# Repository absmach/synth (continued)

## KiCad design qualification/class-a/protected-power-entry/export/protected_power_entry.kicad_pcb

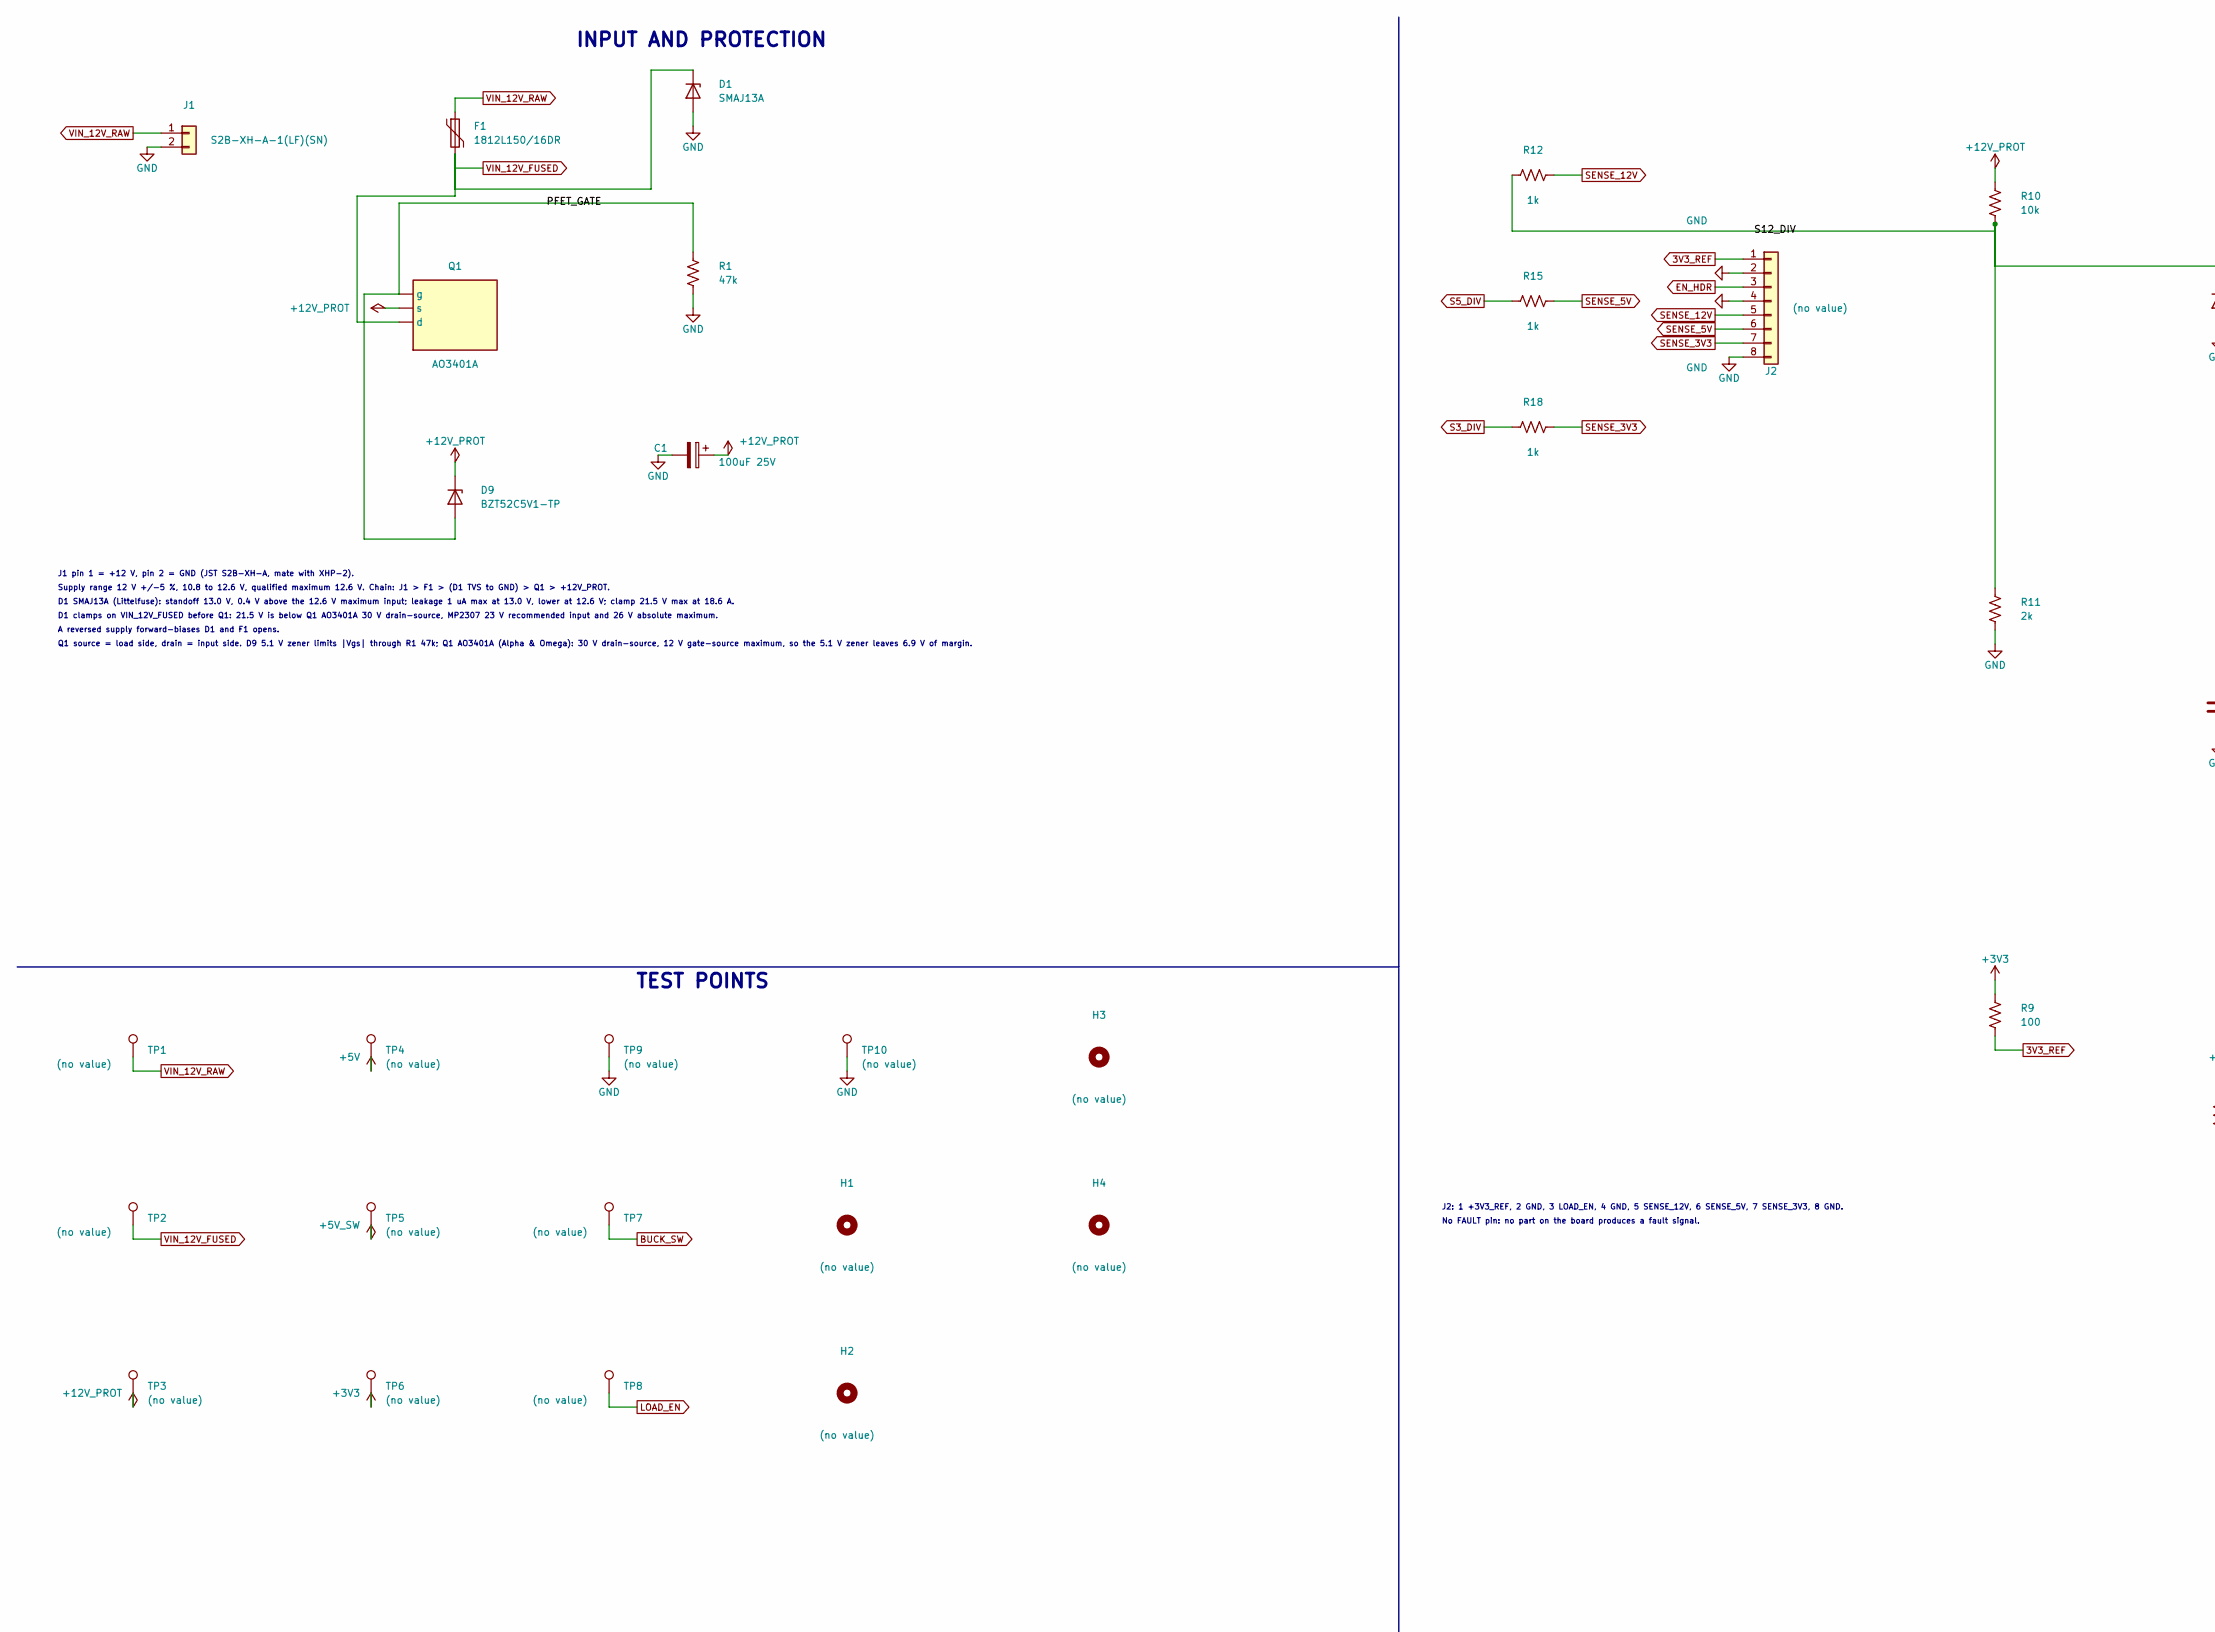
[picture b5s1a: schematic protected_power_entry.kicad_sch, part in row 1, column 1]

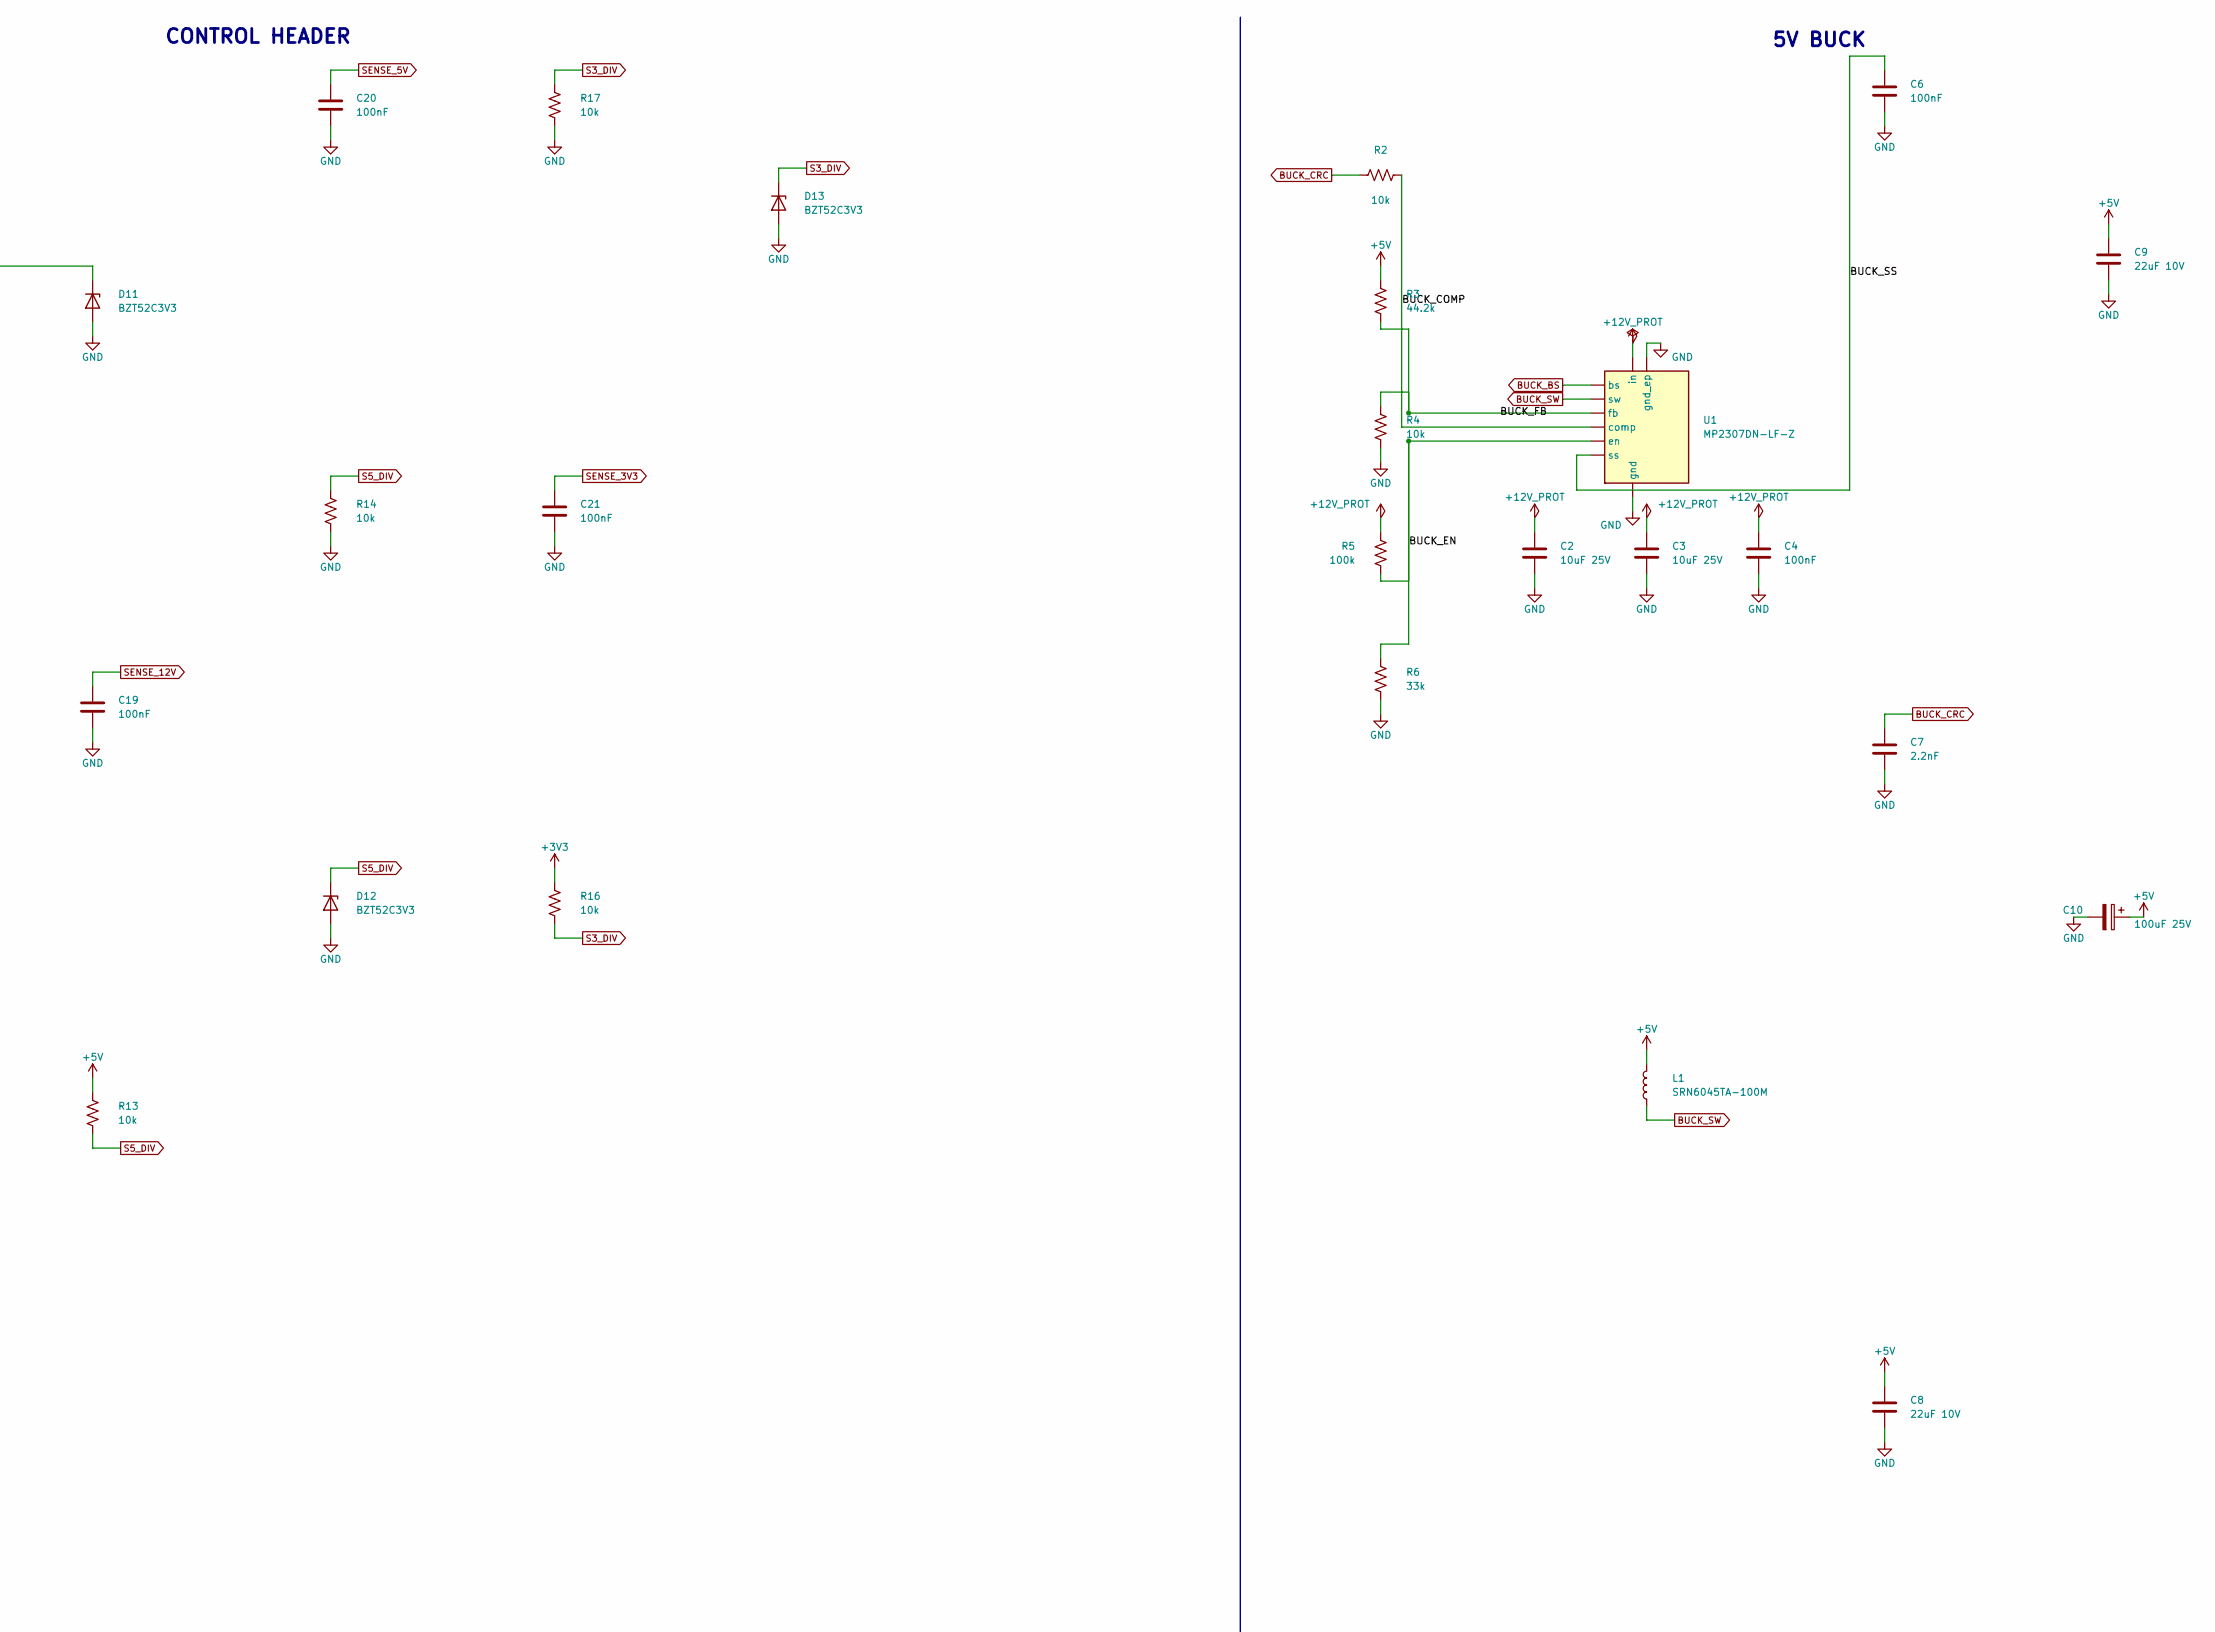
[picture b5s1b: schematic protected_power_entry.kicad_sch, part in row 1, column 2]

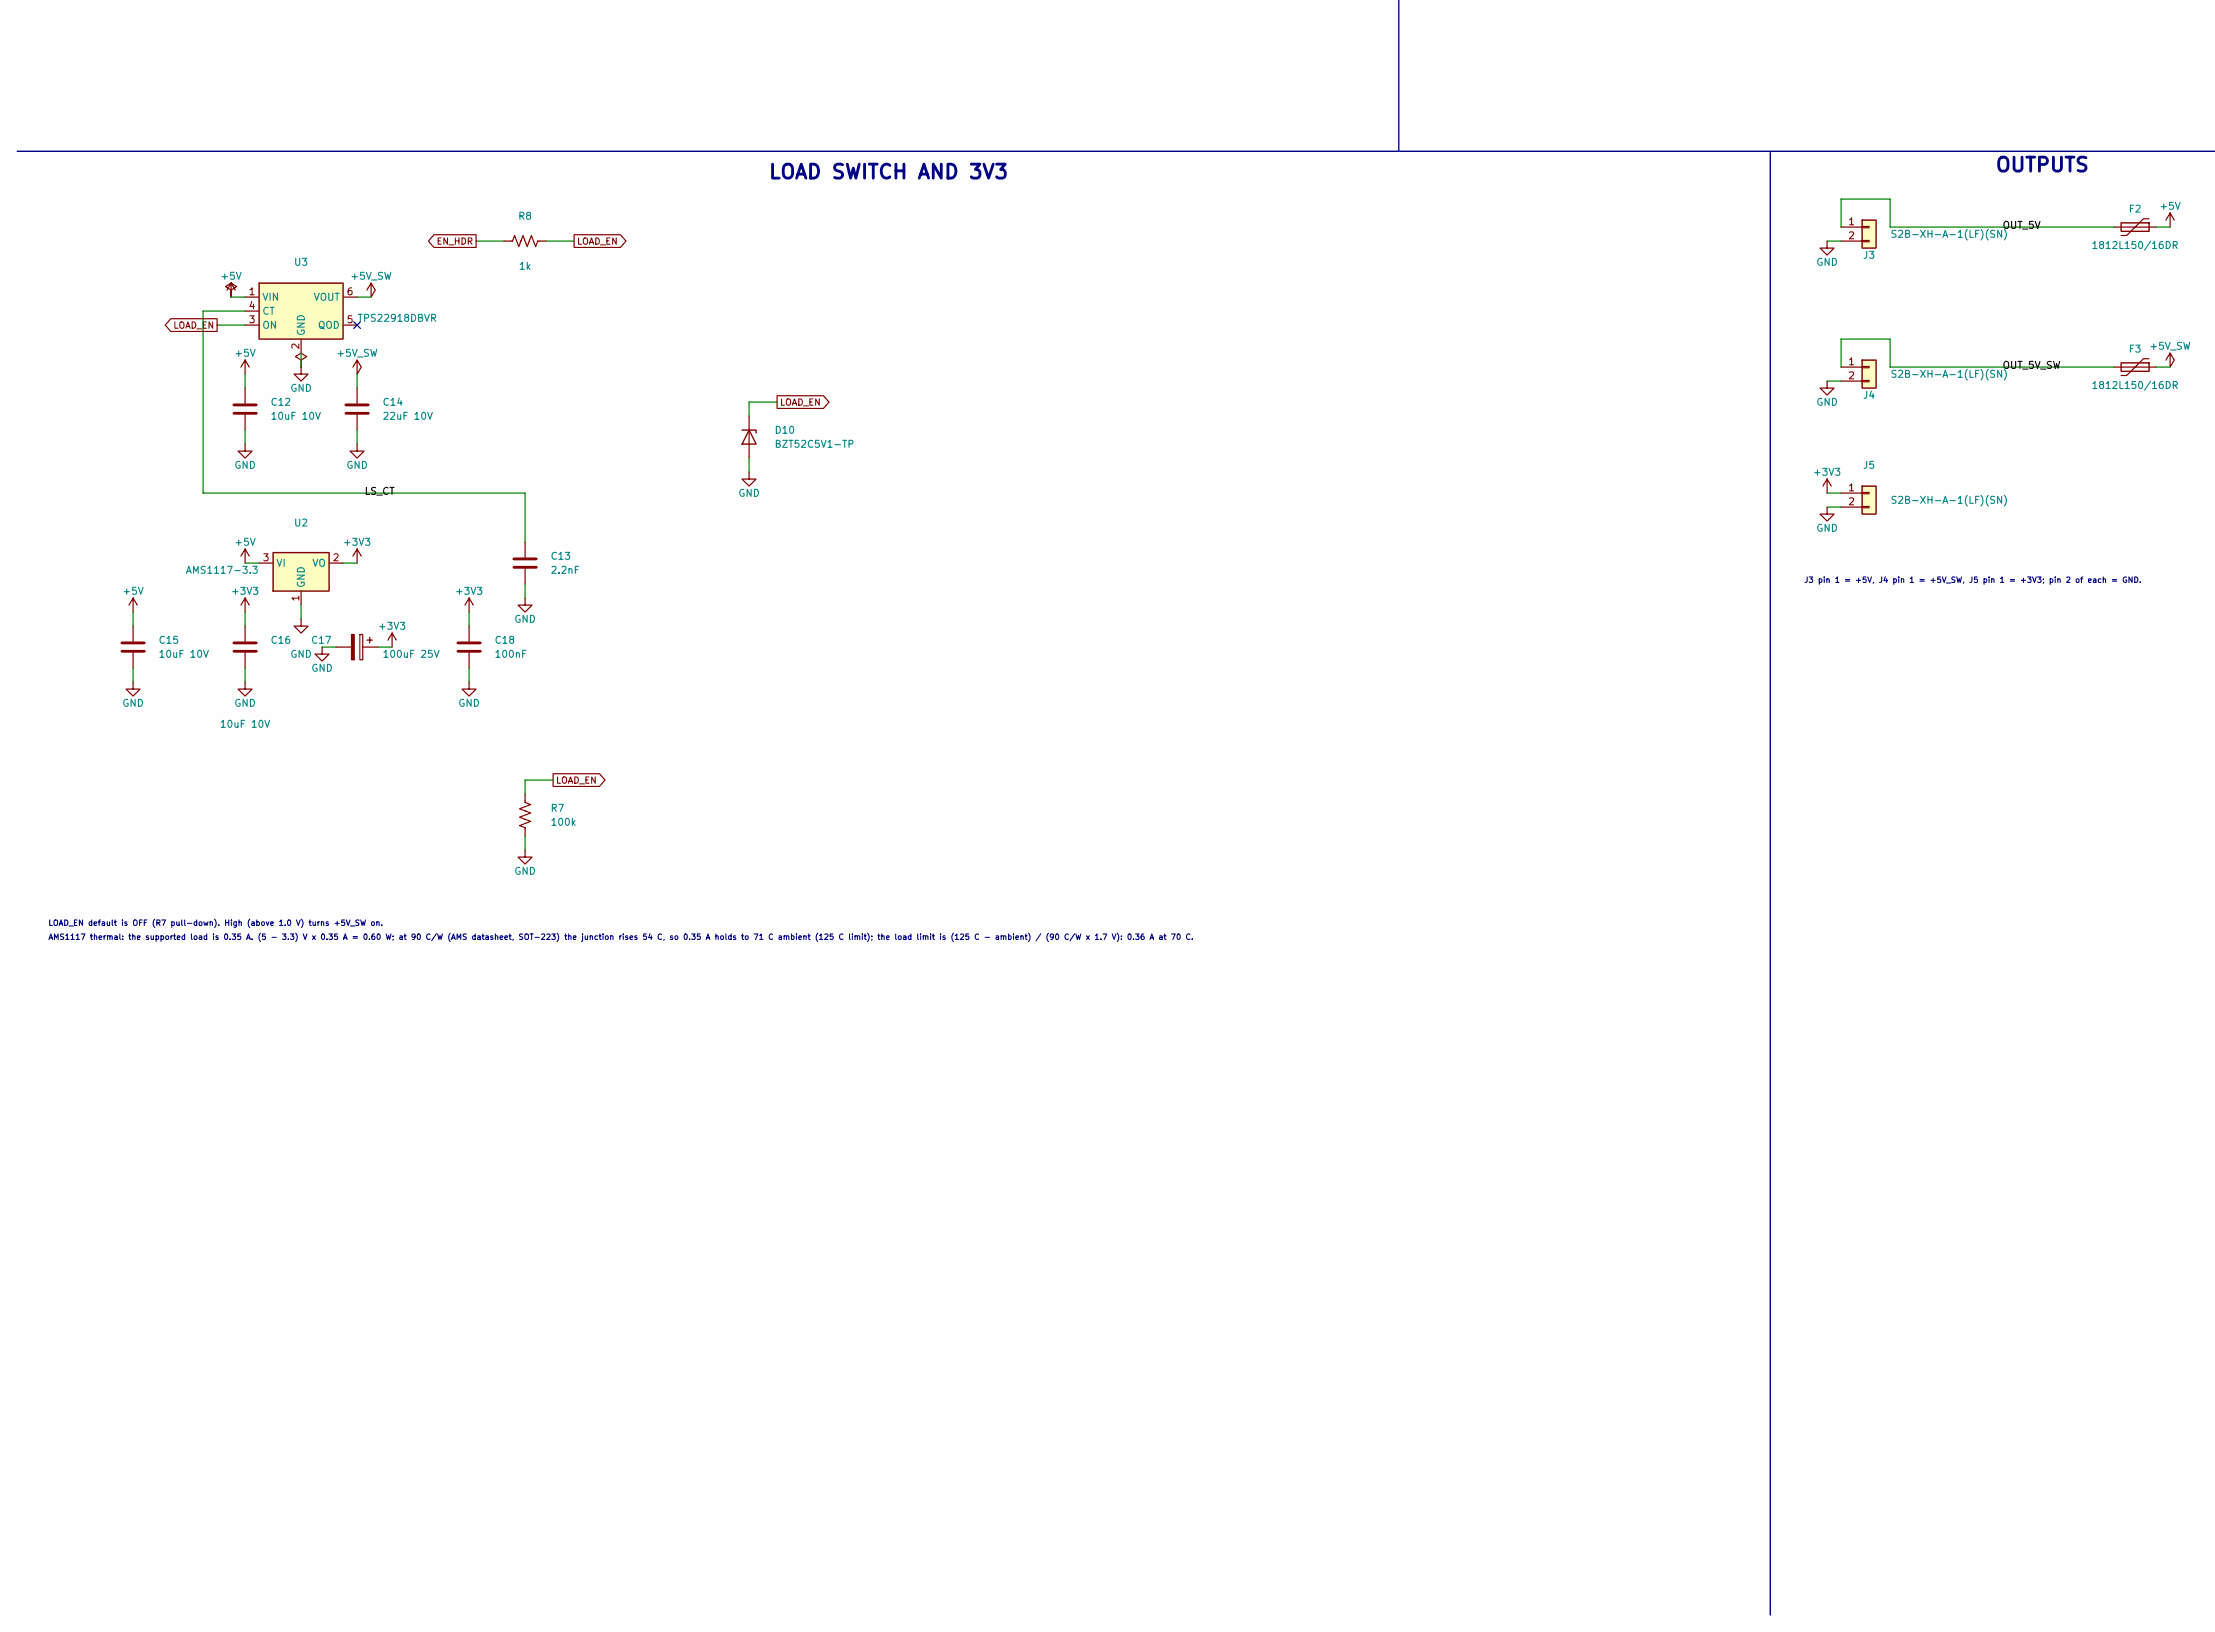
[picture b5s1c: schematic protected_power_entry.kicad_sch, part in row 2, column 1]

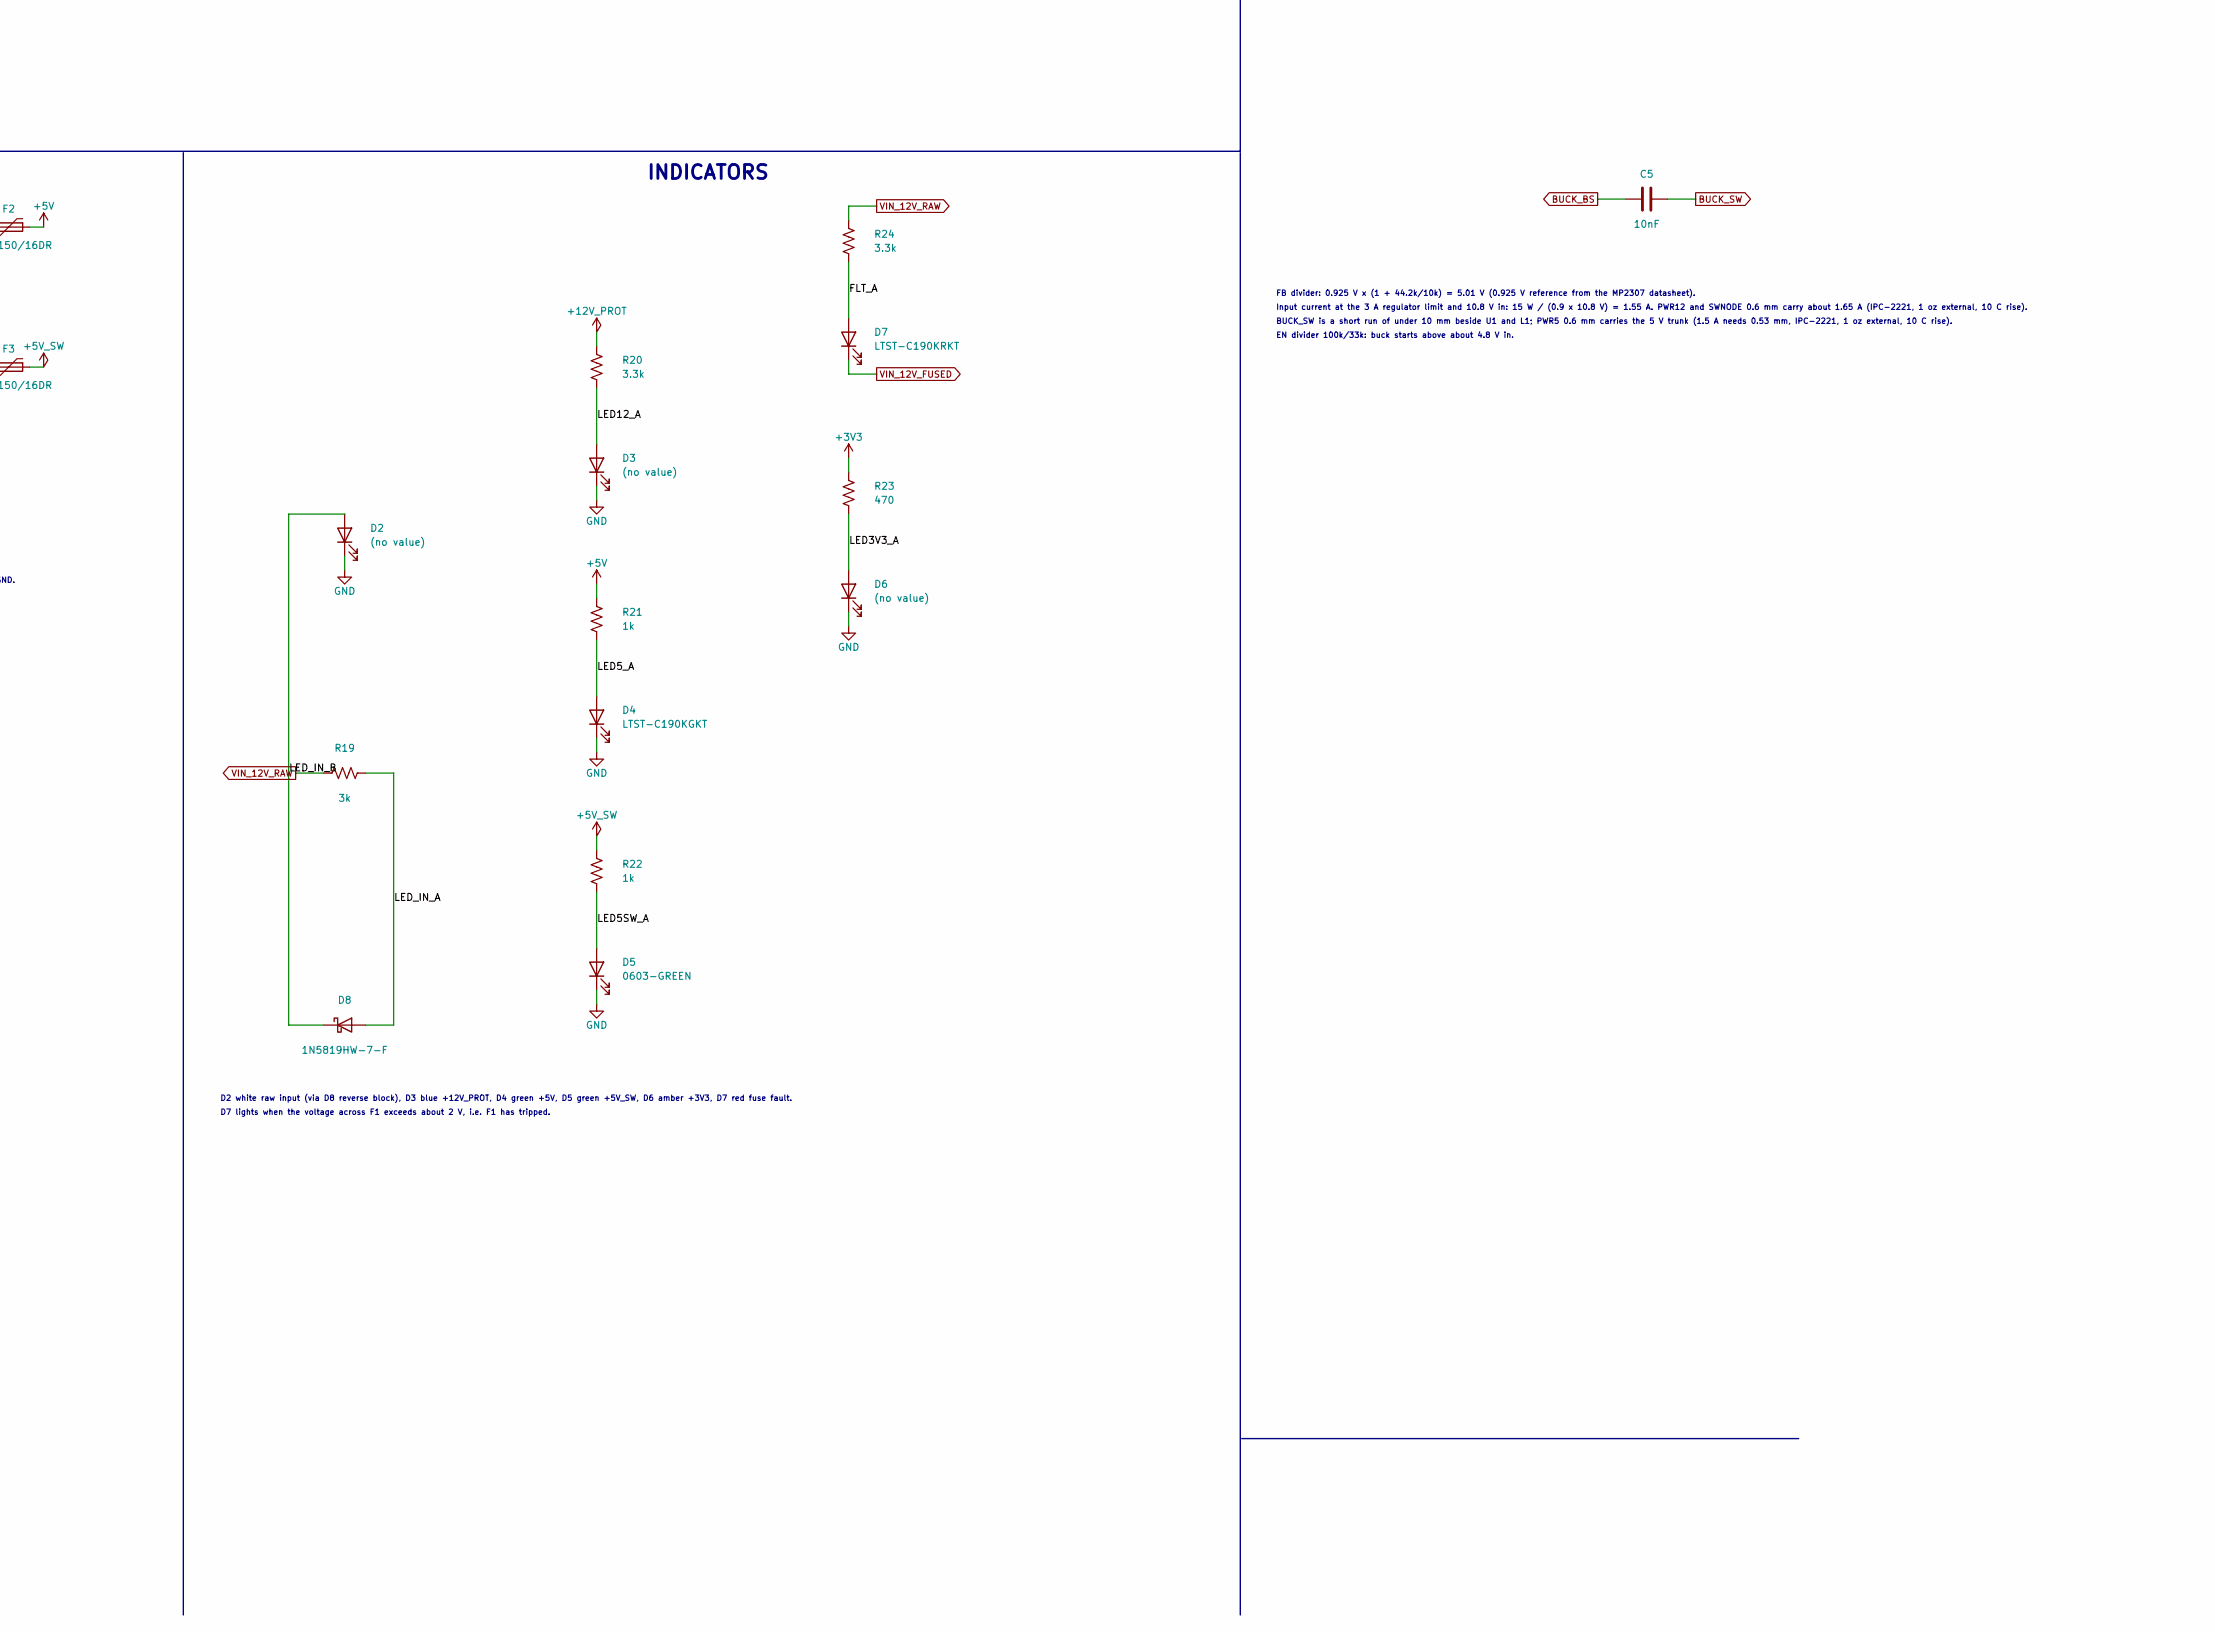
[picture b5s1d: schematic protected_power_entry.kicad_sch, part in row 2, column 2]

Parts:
C1, C10, C17: 100uF 25V; CP_Radial_D6.3mm_P2.50mm
C2, C3: 10uF 25V; C_1206_3216Metric
C4, C6, C18, C19, C20, C21: 100nF; C_0603_1608Metric
C5: 10nF; C_0603_1608Metric
C7, C13: 2.2nF; C_0603_1608Metric
C8, C9, C14: 22uF 10V; C_1206_3216Metric
C12, C15, C16: 10uF 10V; C_1206_3216Metric
D1: SMAJ13A; D_SMA; MPN SMAJ13A
D2, D3, D6: (no value); LED_0603_1608Metric
D4: LTST-C190KGKT; LED_0603_1608Metric; MPN LTST-C190KGKT
D5: 0603-GREEN; LED_0603_1608Metric; MPN 0603-GREEN; LCSC C72043
D7: LTST-C190KRKT; LED_0603_1608Metric; MPN LTST-C190KRKT
D8: 1N5819HW-7-F; D_SOD-123; MPN 1N5819HW-7-F; LCSC C82544
D9, D10: BZT52C5V1-TP; D_SOD-123; MPN BZT52C5V1-TP; LCSC C78728
D11, D12, D13: BZT52C3V3; D_SOD-123; MPN BZT52C3V3
F1, F2, F3: 1812L150/16DR; Fuse_1812_4532Metric; MPN 1812L150/16DR; LCSC C207070
H1, H2, H3, H4: (no value); MountingHole_2.5mm
J1, J3, J4, J5: S2B-XH-A-1(LF)(SN); JST_XH_S2B-XH-A-1_1x02_P2.50mm_Horizontal; MPN S2B-XH-A-1(LF)(SN); LCSC C163035
J2: (no value); PinHeader_1x08_P2.54mm_Vertical
L1: SRN6045TA-100M; L_Bourns_SRN6045TA; MPN SRN6045TA-100M
Q1: AO3401A; SOT-23; MPN AO3401A
R1: 47k; R_0603_1608Metric
R2, R4, R10, R13, R14, R16, R17: 10k; R_0603_1608Metric
R3: 44.2k; R_0603_1608Metric
R5, R7: 100k; R_0603_1608Metric
R6: 33k; R_0603_1608Metric
R8, R12, R15, R18, R21, R22: 1k; R_0603_1608Metric
R9: 100; R_0603_1608Metric
R11: 2k; R_0603_1608Metric
R19: 3k; R_0603_1608Metric
R20, R24: 3.3k; R_0603_1608Metric
R23: 470; R_0603_1608Metric
TP1, TP2, TP3, TP4, TP5, TP6, TP7, TP8, TP9, TP10: (no value); TestPoint_Pad_D1.5mm
U1: MP2307DN-LF-Z; SOIC-8-1EP_3.9x4.9mm_P1.27mm_EP2.41x3.3mm; MPN MP2307DN-LF-Z; LCSC C18921
U2: AMS1117-3.3; SOT-223-3_TabPin2; MPN AMS1117-3.3; LCSC C6186
U3: TPS22918DBVR; SOT-23-6; MPN TPS22918DBVR; LCSC C131941

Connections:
3V3_REF: J2.1, R9.2
+3V3: C16.1, C17.1, C18.1, J5.1, R9.1, R16.1, R23.1, TP6.1, U2.2 (VO)
+5V: C8.1, C9.1, C10.1, C12.1, C15.1, F2.1, L1.2, R3.1, R13.1, R21.1, TP4.1, U2.3 (VI), U3.1 (VIN)
+5V_SW: C14.1, F3.1, R22.1, TP5.1, U3.6 (VOUT)
+12V_PROT: C1.1, C2.1, C3.1, C4.1, D9.1 (K), Q1.2 (s), R5.1, R10.1, R20.1, TP3.1, U1.2 (in)
BUCK_BS: C5.1, U1.1 (bs)
BUCK_COMP: R2.1, U1.6 (comp)
BUCK_CRC: C7.1, R2.2
BUCK_EN: R5.2, R6.1, U1.7 (en)
BUCK_FB: R3.2, R4.1, U1.5 (fb)
BUCK_SS: C6.1, U1.8 (ss)
BUCK_SW: C5.2, L1.1, TP7.1, U1.3 (sw)
EN_HDR: J2.3, R8.1
FLT_A: D7.2 (A), R24.2
GND: C1.2, C2.2, C3.2, C4.2, C6.2, C7.2, C8.2, C9.2, C10.2, C12.2, C13.2, C14.2, C15.2, C16.2, C17.2, C18.2, C19.2, C20.2, C21.2, D1.2 (A), D2.1 (K), D3.1 (K), D4.1 (K), D5.1 (K), D6.1 (K), D10.2 (A), D11.2 (A), D12.2 (A), D13.2 (A), J1.2, J2.2, J2.4, J2.8, J3.2, J4.2, J5.2, R1.2, R4.2, R6.2, R7.2, R11.2, R14.2, R17.2, TP9.1, TP10.1, U1.4 (gnd), U1.9 (gnd_ep), U2.1 (GND), U3.2 (GND)
LED3V3_A: D6.2 (A), R23.2
LED5SW_A: D5.2 (A), R22.2
LED5_A: D4.2 (A), R21.2
LED12_A: D3.2 (A), R20.2
LED_IN_A: D8.2 (A), R19.2
LED_IN_B: D2.2 (A), D8.1 (K)
LOAD_EN: D10.1 (K), R7.1, R8.2, TP8.1, U3.3 (ON)
LS_CT: C13.1, U3.4 (CT)
OUT_5V: F2.2, J3.1
OUT_5V_SW: F3.2, J4.1
PFET_GATE: D9.2 (A), Q1.1 (g), R1.1
S3_DIV: D13.1 (K), R16.2, R17.1, R18.1
S5_DIV: D12.1 (K), R13.2, R14.1, R15.1
S12_DIV: D11.1 (K), R10.2, R11.1, R12.1
SENSE_3V3: C21.1, J2.7, R18.2
SENSE_5V: C20.1, J2.6, R15.2
SENSE_12V: C19.1, J2.5, R12.2
VIN_12V_FUSED: D1.1 (K), D7.1 (K), F1.2, Q1.3 (d), TP2.1
VIN_12V_RAW: F1.1, J1.1, R19.1, R24.1, TP1.1

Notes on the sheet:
INPUT AND PROTECTION
5V BUCK
LOAD SWITCH AND 3V3
OUTPUTS
CONTROL HEADER
INDICATORS
TEST POINTS
J1 pin 1 = +12 V, pin 2 = GND (JST S2B-XH-A, mate with XHP-2).
Supply range 12 V +/-5 %, 10.8 to 12.6 V, qualified maximum 12.6 V. Chain: J1 > F1 > (D1 TVS to GND) > Q1 > +12V_PROT.
D1 SMAJ13A (Littelfuse): standoff 13.0 V, 0.4 V above the 12.6 V maximum input; leakage 1 uA max at 13.0 V, lower at 12.6 V; clamp 21.5 V max at 18.6 A.
D1 clamps on VIN_12V_FUSED before Q1: 21.5 V is below Q1 AO3401A 30 V drain-source, MP2307 23 V recommended input and 26 V absolute maximum.
A reversed supply forward-biases D1 and F1 opens.
Q1 source = load side, drain = input side. D9 5.1 V zener limits |Vgs| through R1 47k; Q1 AO3401A (Alpha & Omega): 30 V drain-source, 12 V gate-source maximum, so the 5.1 V zener leaves 6.9 V of margin.
FB divider: 0.925 V x (1 + 44.2k/10k) = 5.01 V (0.925 V reference from the MP2307 datasheet).
Input current at the 3 A regulator limit and 10.8 V in: 15 W / (0.9 x 10.8 V) = 1.55 A. PWR12 and SWNODE 0.6 mm carry about 1.65 A (IPC-2221, 1 oz external, 10 C rise).
BUCK_SW is a short run of under 10 mm beside U1 and L1; PWR5 0.6 mm carries the 5 V trunk (1.5 A needs 0.53 mm, IPC-2221, 1 oz external, 10 C rise).
EN divider 100k/33k: buck starts above about 4.8 V in.
LOAD_EN default is OFF (R7 pull-down). High (above 1.0 V) turns +5V_SW on.
AMS1117 thermal: the supported load is 0.35 A. (5 - 3.3) V x 0.35 A = 0.60 W; at 90 C/W (AMS datasheet, SOT-223) the junction rises 54 C, so 0.35 A holds to 71 C ambient (125 C limit); the load limit is (125 C - ambient) / (90 C/W x 1.7 V): 0.36 A at 70 C.
J3 pin 1 = +5V, J4 pin 1 = +5V_SW, J5 pin 1 = +3V3; pin 2 of each = GND.
J2: 1 +3V3_REF, 2 GND, 3 LOAD_EN, 4 GND, 5 SENSE_12V, 6 SENSE_5V, 7 SENSE_3V3, 8 GND.
No FAULT pin: no part on the board produces a fault signal.
D2 white raw input (via D8 reverse block), D3 blue +12V_PROT, D4 green +5V, D5 green +5V_SW, D6 amber +3V3, D7 red fuse fault.
D7 lights when the voltage across F1 exceeds about 2 V, i.e. F1 has tripped.
